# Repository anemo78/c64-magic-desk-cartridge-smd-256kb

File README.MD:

# C64 Magic Desk Cartridge 256kb (SMD version)

This version of the Magic Desk compatible cartridge uses mainly SMD components and supports 28* and 32** pin (E)EPROM and FLASH memory chips **up to 256kB**. The type of memory chip is configured with a solder bridge on the back of the PCB.

The Magic Desk cartridge was originally created by Commodore. Marko Šolajić and Žarko Živanov then utilized the same memory bank switching technique and created the [Magic Desk Cart Generator 2.0](https://csdb.dk/release/?id=132937). ***Please note that the MDCG is now available in version 3.0 and supports up to 1MB memory with slightly different hardware.***

***28-pin:**
M27512, M27C512, AM27C512, W27C512, W27E512, 27SF512, 39SF512 and more

****32-pin:**
M27C2001, M27C1001, NM27C020, NM27C010, AT29C020, AT29C010, 39SF010A, 39SF020A and more

**The MDCG project is available under GNU GENERAL PUBLIC LICENSE.**

## Bill of materials (BOM)

| Name | Component |
|--|--|
| U1 | DIP 28/32 (E)EPROM/FLASH memory (see above) |
| U2 | 74LS02D SO-14 (or HCT) |
| U3 | 74LS174D SO-16 (or HCT) |
| C1-C2 | 100nF 0805 size capacitor |
| R1 | 10k 0805 size resistor |
| S1 | TACT switch (SCHURTER 1301.9303 for instance) |

## PCB Images

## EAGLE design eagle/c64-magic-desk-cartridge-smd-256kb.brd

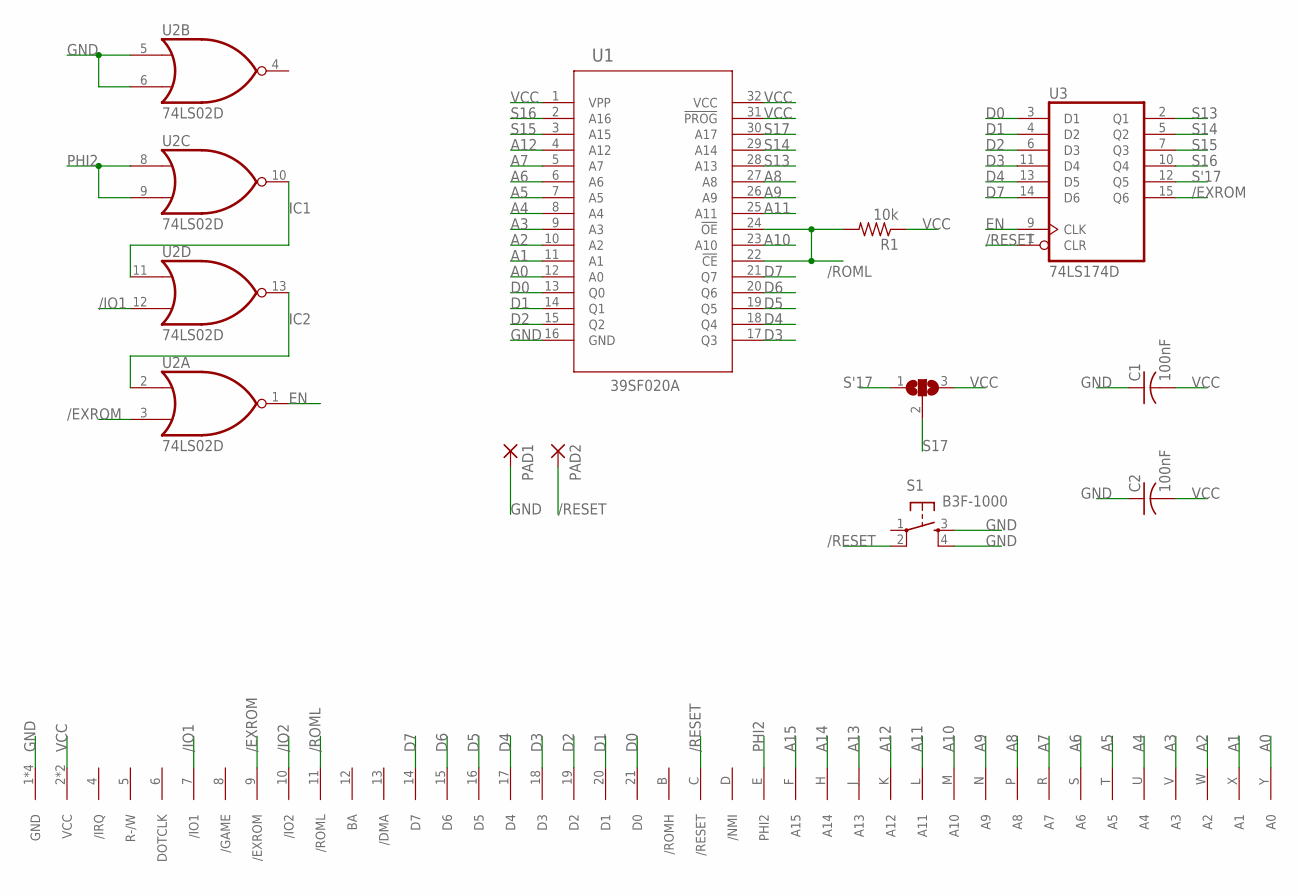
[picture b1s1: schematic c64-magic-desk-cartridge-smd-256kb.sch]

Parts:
C1, C2: 100nF; C0805K
PAD1, PAD2: SMD2.54-5.08; SMD2,54-5,08
R1: 10k; R0805
S1: B3F-1000; B3F-10XX
SJ1: SJ2W; SJ_2
U1: M27C2001DIP32-LOWERED; DIP32
U2: 74LS02D; SO14
U3: 74LS174D; SO16
U$1: C64-EXPANSION-PORT; EXPANSION_PORT

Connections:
/EXROM: U2.3 (I1), U3.15 (Q6), U$1.9 (/EXROM)
/IO1: U2.12 (I1), U$1.7 (/IO1)
/IO2: U$1.10 (/IO2)
/RESET: PAD2.P$1, S1.2 (P1), U3.1 (CLR), U$1.C (/RESET)
/ROML: R1.2, U1.22 (!CE), U1.24 (!OE), U$1.11 (/ROML)
A0: U1.12 (A0), U$1.Y (A0)
A1: U1.11 (A1), U$1.X (A1)
A2: U1.10 (A2), U$1.W (A2)
A3: U1.9 (A3), U$1.V (A3)
A4: U1.8 (A4), U$1.U (A4)
A5: U1.7 (A5), U$1.T (A5)
A6: U1.6 (A6), U$1.S (A6)
A7: U1.5 (A7), U$1.R (A7)
A8: U1.27 (A8), U$1.P (A8)
A9: U1.26 (A9), U$1.N (A9)
A10: U1.23 (A10), U$1.M (A10)
A11: U1.25 (A11), U$1.L (A11)
A12: U1.4 (A12), U$1.K (A12)
A13: U$1.J (A13)
A14: U$1.H (A14)
A15: U$1.F (A15)
D0: U1.13 (Q0), U3.3 (D1), U$1.21 (D0)
D1: U1.14 (Q1), U3.4 (D2), U$1.20 (D1)
D2: U1.15 (Q2), U3.6 (D3), U$1.19 (D2)
D3: U1.17 (Q3), U3.11 (D4), U$1.18 (D3)
D4: U1.18 (Q4), U3.13 (D5), U$1.17 (D4)
D5: U1.19 (Q5), U$1.16 (D5)
D6: U1.20 (Q6), U$1.15 (D6)
D7: U1.21 (Q7), U3.14 (D6), U$1.14 (D7)
EN: U2.1 (O), U3.9 (CLK)
GND: C1.1, C2.1, PAD1.P$1, S1.3 (S), S1.4 (S1), U1.16 (GND), U2.5 (I0), U2.6 (I1), U2.7 (GND), U3.8 (GND), U$1.1 (GND), U$1.22 (GND), U$1.A (GND), U$1.Z (GND)
IC1: U2.10 (O), U2.11 (I0)
IC2: U2.2 (I0), U2.13 (O)
PHI2: U2.8 (I0), U2.9 (I1), U$1.E (PHI2)
S13: U1.28 (A13), U3.2 (Q1)
S14: U1.29 (A14), U3.5 (Q2)
S15: U1.3 (A15), U3.7 (Q3)
S16: U1.2 (A16), U3.10 (Q4)
S17: SJ1.2, U1.30 (A17)
S'17: SJ1.1, U3.12 (Q5)
VCC: C1.2, C2.2, R1.1, SJ1.3, U1.1 (VPP), U1.31 (!PROG), U1.32 (VCC), U2.14 (VCC), U3.16 (VCC), U$1.2 (VCC), U$1.3 (VCC)

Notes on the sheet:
39SF020A

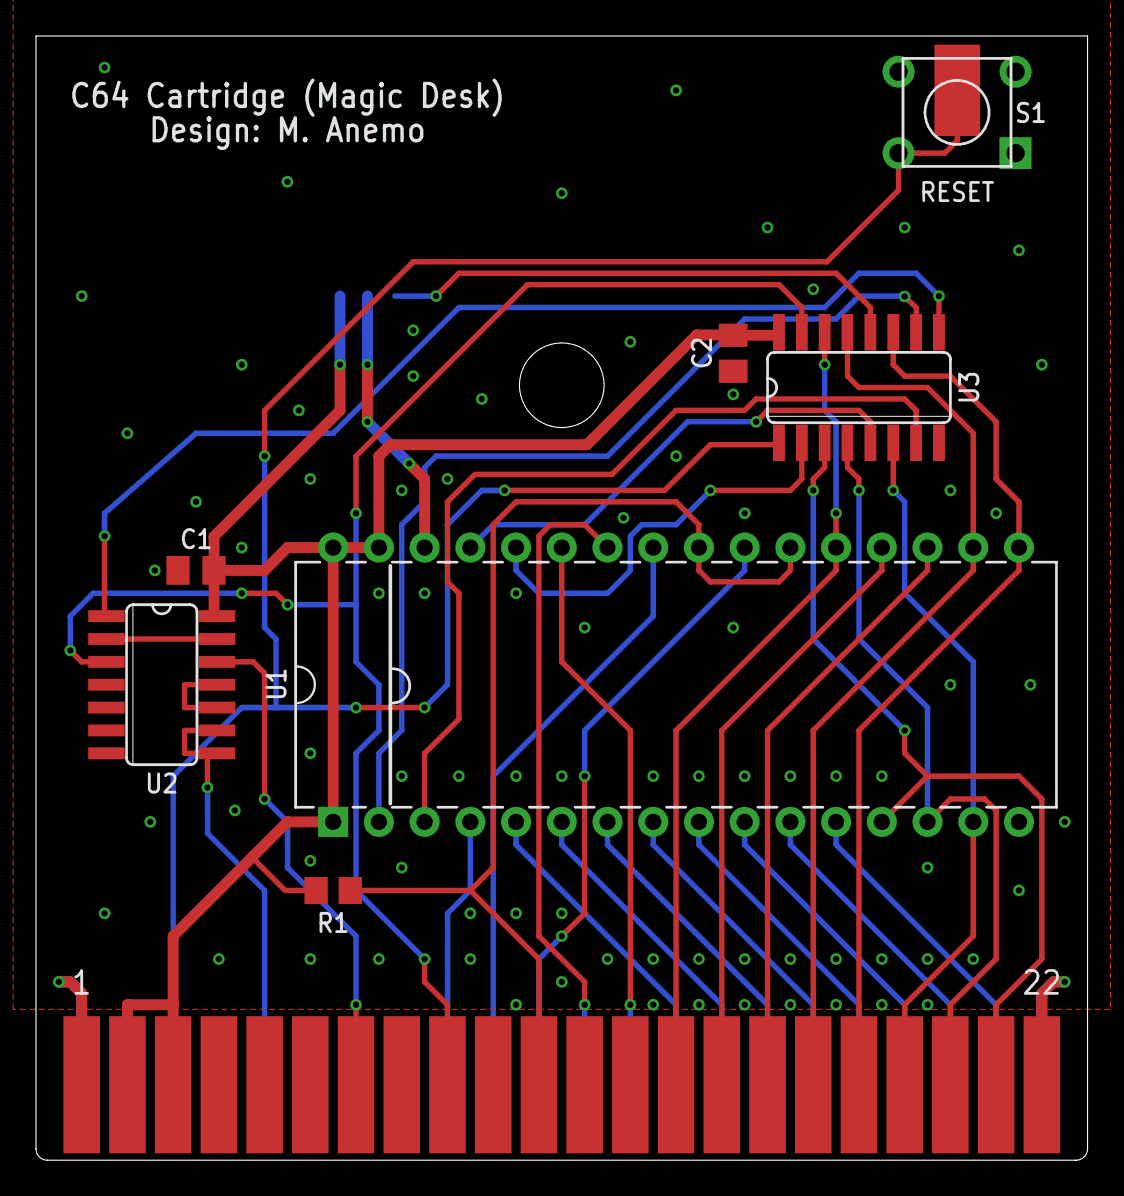
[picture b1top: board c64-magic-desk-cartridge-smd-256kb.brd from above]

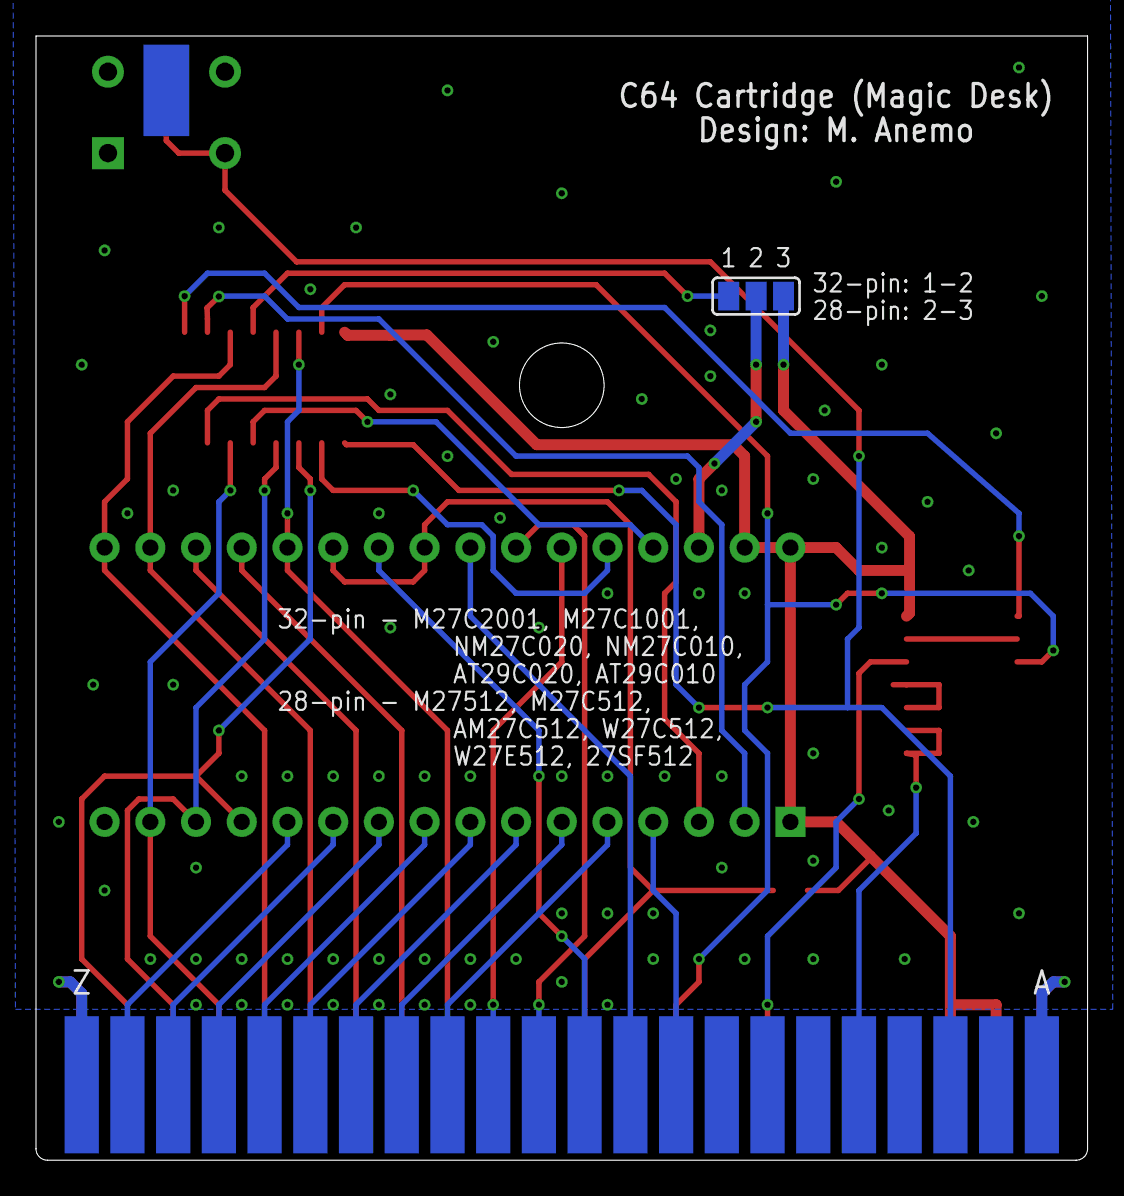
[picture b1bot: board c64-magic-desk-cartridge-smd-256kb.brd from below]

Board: 2 copper layers, 58.4 x 62.5 mm, 11 parts (2 on the bottom side), 37 nets.

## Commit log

2019-09-30 added pcb images
2019-09-30 moved eagle files to own folder
2019-09-30 updated board text
